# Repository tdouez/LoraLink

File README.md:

// ███████╗██████╗ ███████╗
// ██╔════╝██╔══██╗██╔════╝
// █████╗  ██████╔╝███████╗
// ██╔══╝  ██╔══██╗╚════██║
// ██║     ██████╔╝███████║
// ╚═╝     ╚═════╝ ╚══════╝
# LoraLink

Module de récupération des données TIC du compteur Linky avec transmission en LoRa

- Description disponible sur http://fumeebleue.fr

------------------------------------------------------------------------------------
Code mise à disposition selon les termes de la Licence Creative Commons Attribution
Pas d’Utilisation Commerciale.
Partage dans les Mêmes Conditions 4.0 International.
------------------------------------------------------------------------------------

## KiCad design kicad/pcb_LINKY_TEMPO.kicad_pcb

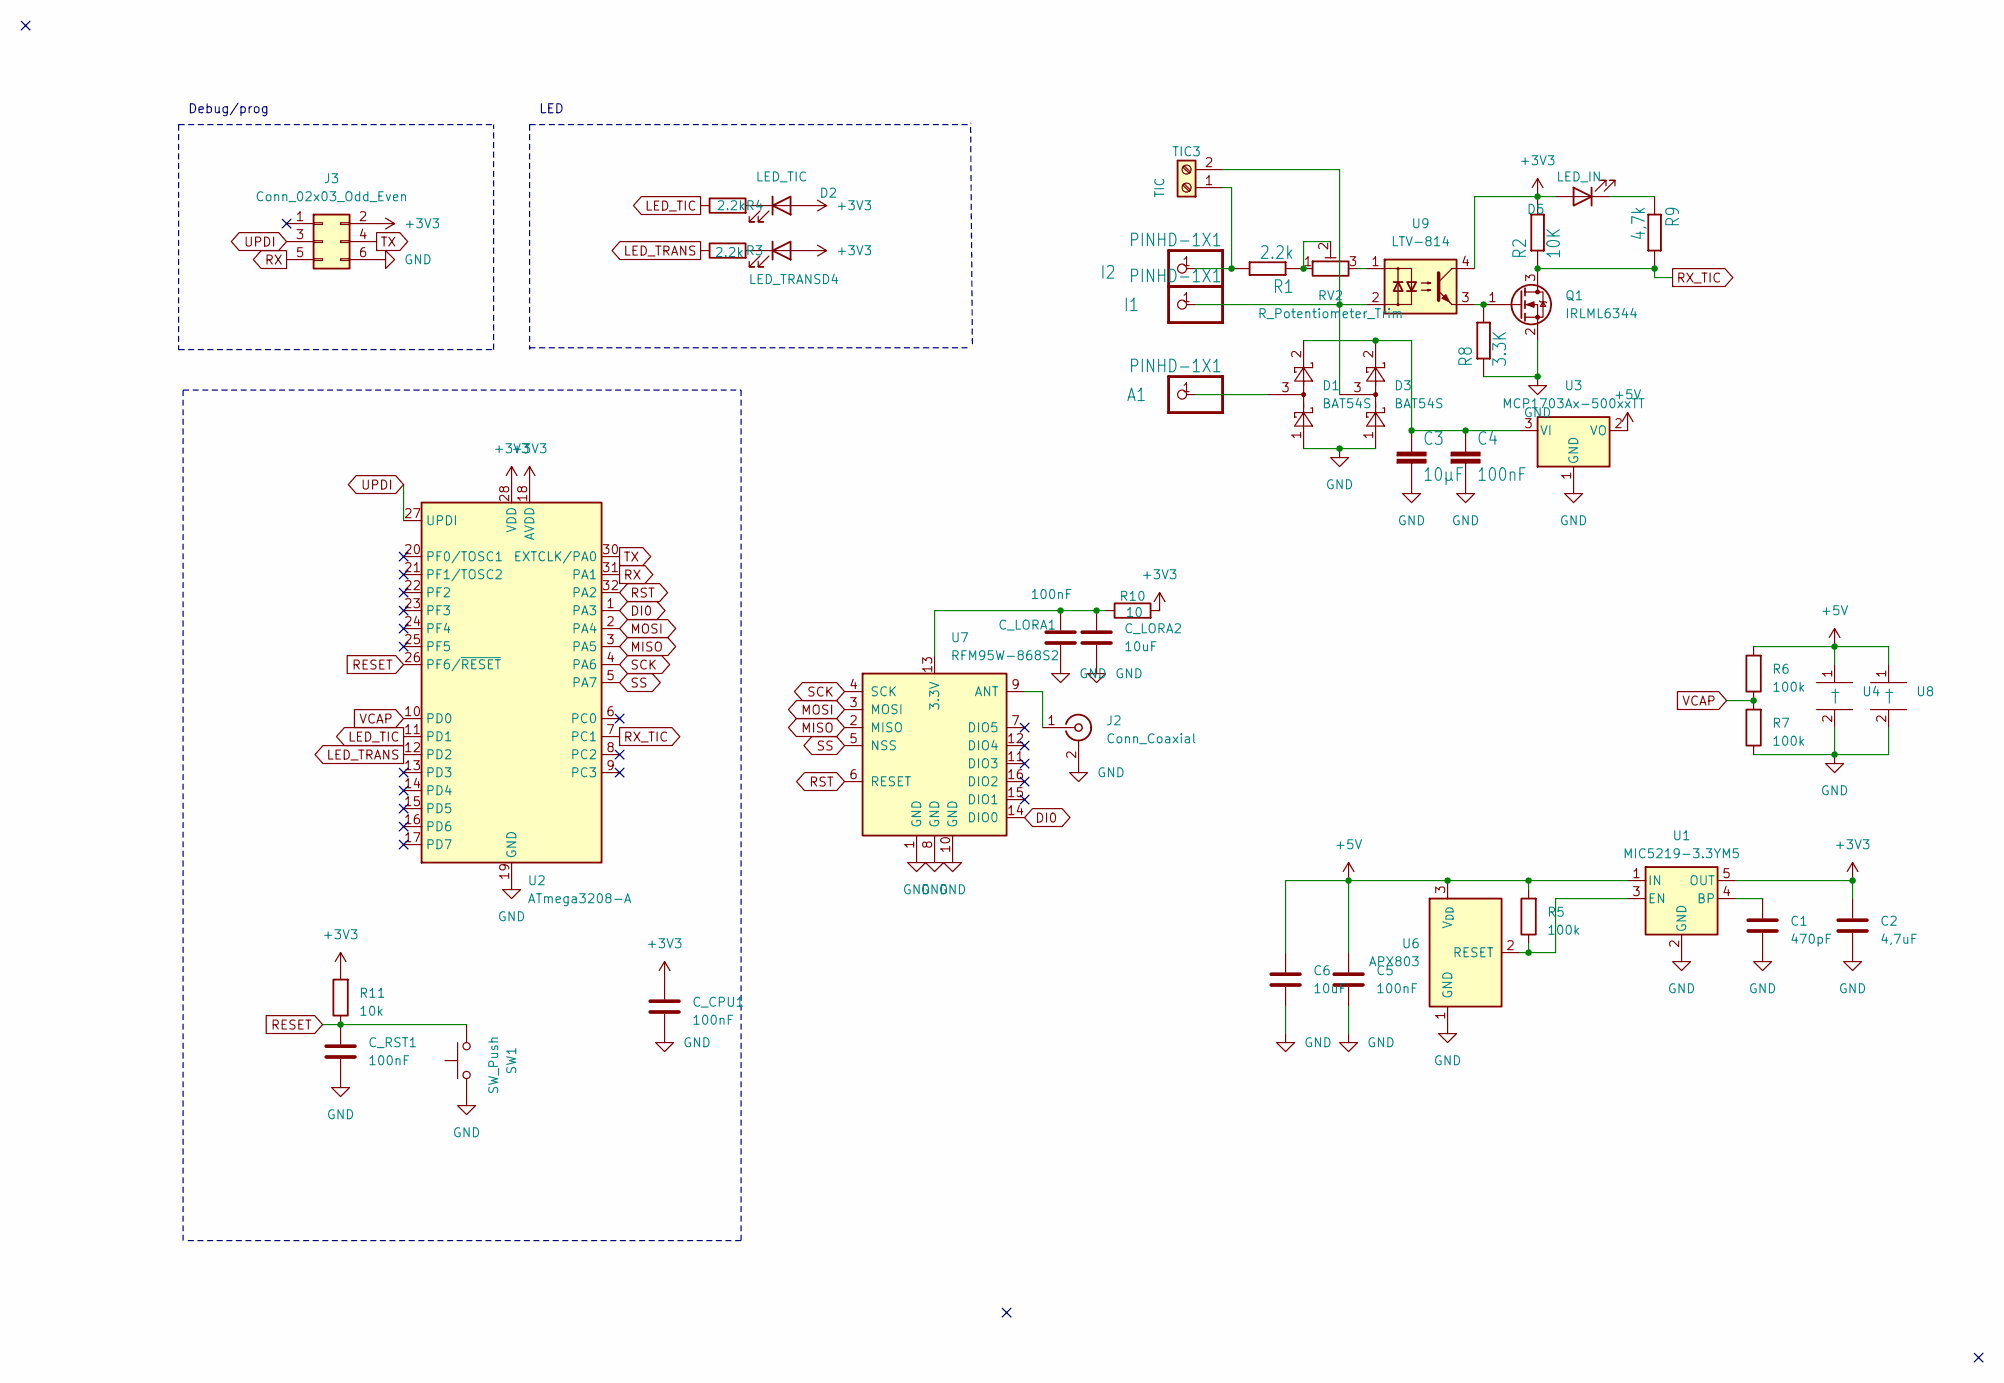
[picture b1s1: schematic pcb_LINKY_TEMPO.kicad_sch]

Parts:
A1: PINHD-1X1; PinHeader_1x01_P2.54mm_Horizontal
C1: 470pF; C_1206_3216Metric_Pad1.33x1.80mm_HandSolder
C2: 4,7uF; C_1206_3216Metric_Pad1.33x1.80mm_HandSolder
C3: 10µF; C_1206_3216Metric_Pad1.33x1.80mm_HandSolder
C4: 100nF; C_1206_3216Metric
C5: 100nF; C_1206_3216Metric_Pad1.33x1.80mm_HandSolder
C6: 10uF; C_1210_3225Metric_Pad1.33x2.70mm_HandSolder
C_CPU1: 100nF; C_1206_3216Metric_Pad1.33x1.80mm_HandSolder
C_LORA1: 100nF; C_1206_3216Metric_Pad1.33x1.80mm_HandSolder
C_LORA2: 10uF; C_1206_3216Metric_Pad1.33x1.80mm_HandSolder
C_RST1: 100nF; C_1206_3216Metric_Pad1.33x1.80mm_HandSolder
D1, D3: BAT54S; SOT-23
D2: LED_TIC; LED_1206_3216Metric_Pad1.42x1.75mm_HandSolder
D4: LED_TRANS; LED_1206_3216Metric_Pad1.42x1.75mm_HandSolder
D5: LED_IN; LED_1206_3216Metric_Pad1.42x1.75mm_HandSolder
I1, I2: PINHD-1X1; PinHeader_1x01_P2.54mm_Horizontal
J2: Conn_Coaxial; U.FL_Molex_MCRF_73412-0110_Vertical
J3: Conn_02x03_Odd_Even; PinSocket_2x03_P2.54mm_Vertical
Q1: IRLML6344; SOT-23
R1, R3, R4: 2.2k; R_1206_3216Metric
R2: 10K; R_1206_3216Metric
R5, R6, R7: 100k; R_1206_3216Metric_Pad1.30x1.75mm_HandSolder
R8: 3.3K; R_1206_3216Metric
R9: 4,7k; R_1206_3216Metric
R10: 10; R_1206_3216Metric
R11: 10k; R_1206_3216Metric_Pad1.30x1.75mm_HandSolder
RV2: R_Potentiometer_Trim; Potentiometer_Bourns_3314S_Horizontal
SW1: SW_Push; SW_SPST_CK_RS282G05A3
TIC3: TIC; Molex_KK-254_AE-6410-02A_1x02_P2.54mm_Vertical
U1: MIC5219-3.3YM5; SOT-23-5
U2: ATmega3208-A; TQFP-32_7x7mm_P0.8mm
U3: MCP1703Ax-500xxTT; SOT-23
U4, U8: Supercapa V 0.68
U6: APX803; SOT-23
U7: RFM95W-868S2; HOPERF_RFM9XW_SMD
U9: LTV-814; DIP-4_W7.62mm_SMDSocket_SmallPads

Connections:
+3V3: C2.2, C_CPU1.2, D2.2 (A), D4.2 (A), D5.2 (A), J3.2, R2.2, R10.2, R11.2, U1.5 (OUT), U2.18 (AVDD), U2.28 (VDD), U9.4
+5V: C5.2, C6.2, R5.2, R6.2, U1.1 (IN), U3.2 (VO), U4.1 (+), U6.3 (V_{DD}), U8.1 (+)
DI0: U2.1 (PA3), U7.14 (DIO0)
GND: C1.1, C2.1, C3.2, C4.2, C5.1, C6.1, C_CPU1.1, C_LORA1.1, C_LORA2.1, C_RST1.1, D1.1, D3.1, J2.2 (Ext), J3.6, Q1.2 (S), R7.1, R8.1, SW1.1, U1.2 (GND), U2.19 (GND), U2.29 (GND), U3.1 (GND), U4.2 (-), U6.1 (GND), U7.1 (GND), U7.8 (GND), U7.10 (GND), U8.2 (-)
LED_TIC: R4.1, U2.11 (PD1)
LED_TRANS: R3.1, U2.12 (PD2)
MISO: U2.3 (PA5), U7.2 (MISO)
MOSI: U2.2 (PA4), U7.3 (MOSI)
unnamed: A1.1, D1.3
unnamed: D2.1 (K), R4.2
unnamed: D4.1 (K), R3.2
unnamed: D5.1 (K), R9.1
unnamed: J2.1 (In), U7.9 (ANT)
unnamed: Q1.1 (G), R8.2, U9.3
unnamed: R1.1, RV2.1, RV2.2
unnamed: RV2.3, U9.1
unnamed: I2.1, R1.2, TIC3.1
unnamed: D3.3, I1.1, TIC3.2, U9.2
unnamed: C1.2, U1.4 (BP)
unnamed: R5.1, U1.3 (EN), U6.2 (RESET)
unnamed: C3.1, C4.1, D1.2, D3.2, U3.3 (VI)
unnamed: C_LORA1.2, C_LORA2.2, R10.1, U7.13 (3.3V)
RESET: C_RST1.2, R11.1, SW1.2, U2.26 (PF6/~RESET)
RST: U2.32 (PA2), U7.6 (RESET)
RX: J3.5, U2.31 (PA1)
RX_TIC: Q1.3 (D), R2.1, R9.2, U2.7 (PC1)
SCK: U2.4 (PA6), U7.4 (SCK)
SS: U2.5 (PA7), U7.5 (NSS)
TX: J3.4, U2.30 (EXTCLK/PA0)
UPDI: J3.3, U2.27 (UPDI)
VCAP: R6.1, R7.2, U2.10 (PD0)

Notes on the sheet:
LED
Debug/prog

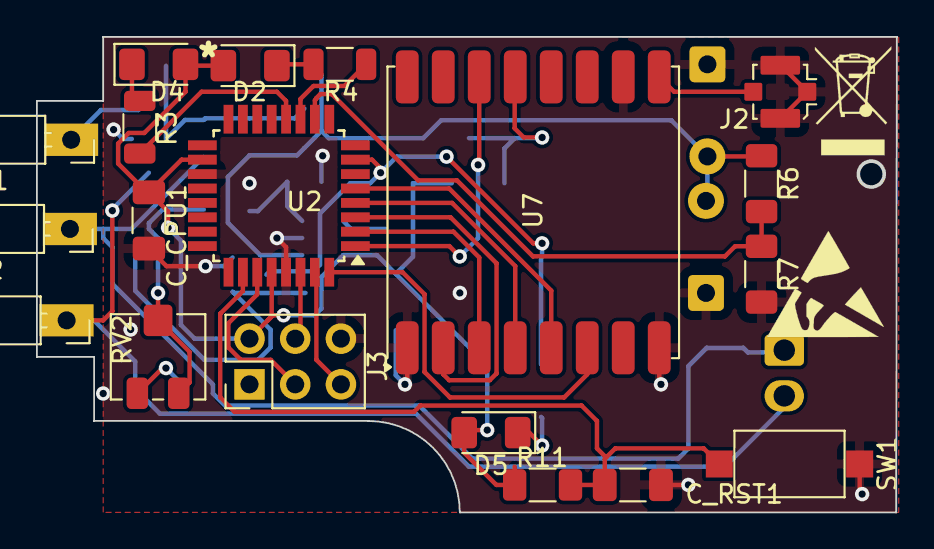
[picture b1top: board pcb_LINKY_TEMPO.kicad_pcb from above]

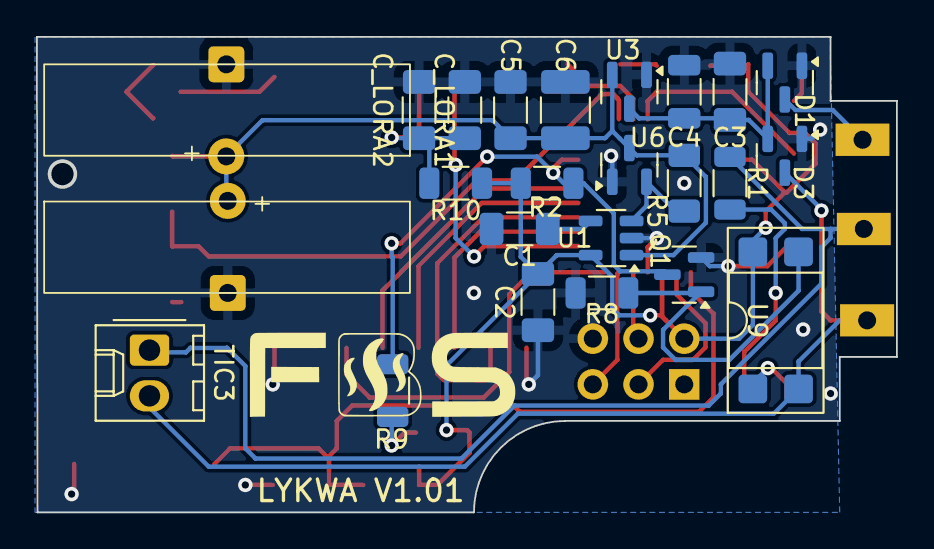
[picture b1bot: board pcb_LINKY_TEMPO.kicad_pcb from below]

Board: 2 copper layers, 47.7 x 26.3 mm, 43 parts (24 on the bottom side), 31 nets.

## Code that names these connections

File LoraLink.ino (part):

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const unsigned long SEND_FREQUENCY_FULL = 600000; // 10 mn, Minimum time between send (in milliseconds).
unsigned long lastTime_LoraSend = 0;
unsigned long lastTime_full = 0;
const int ledTicPin = PIN_PD1;
const int ledInfoPin = PIN_PD2;
const int vcapPin = PIN_PD0;

const long frequency = 868E6; 	// LoRa Frequency
const int csPin = PIN_PA7; 		// LoRa radio chip select
const int resetPin = PIN_PF6; 	// LoRa radio reset
const int irqPin = PIN_PA3; 	// interrupt pin

const char char_ADCO[] PROGMEM = "ADCO";
const char char_ADSC[] PROGMEM = "ADSC";
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_Mode_e mode_tic;
TInfo tinfo;
PayloadData payload_data;
auto led = JLed(PIN_PD2).Breathe(2000).Forever();



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
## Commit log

2025-07-28 LoraLink
2025-08-01 V1.0.1
    Ajout calcul Toa (Time On Air)
2025-08-05 v1.02
    Optimisation du payload Lora
2025-08-14 V1.03
    Correction sur le num compteur

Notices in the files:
LoraLink.ino:
Copyright (C) 2025 FBS. Tous droits réservés.
